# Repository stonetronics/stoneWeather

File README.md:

# stoneweather
Small IOT Weather station using Wifi Module WeMos D1 Mini, Pressure/Temperature Sensor HP03S, Relative Air Humidity/Temperature Sensor HTU21 LDO AMS1117

Newer version using WeMos D1 Mini, kicking out the ATmega328 to reduce complexity

Hardware Layout drawn in Eagle 8.0
coming soon!

Code for WeMos D1 Mini written in Arduino IDE (esp8266_d1mini_weather_station_v2)
-Measures temperature and air pressure using HP03s (custom .cpp and .h mixed up of "github.com/philippG777/HP03S" and "codebender.cc/sketch:42077#HP03S.ino"
-Measures temperature and relative air humidity using HTU21 (sparkfun Library)
-Displays all Data on a very simple Website to be used by a data collector (see github.com/ringo96/weatherstation)

Old Version using ATmega328 and ESP8266:

Hardware Layout drawn in Eagle 8.0
-Header for ESP8266 and GY21-HTU21 breakout boards mounted SMD
-all components SMD except for LED and XTAL

Code for ESP8266 written in Arduino IDE (esp8266displayUart)
-Reads temperature and air pressure on uart and displays it on a very simple website to be used by a data collector (see github.com/ringo96/weatherstation)

Code for ATMega328 written in Arduino IDE (HP03sUART)
-Measures temperature and air pressure with an HP03S sensor and displays it on uart

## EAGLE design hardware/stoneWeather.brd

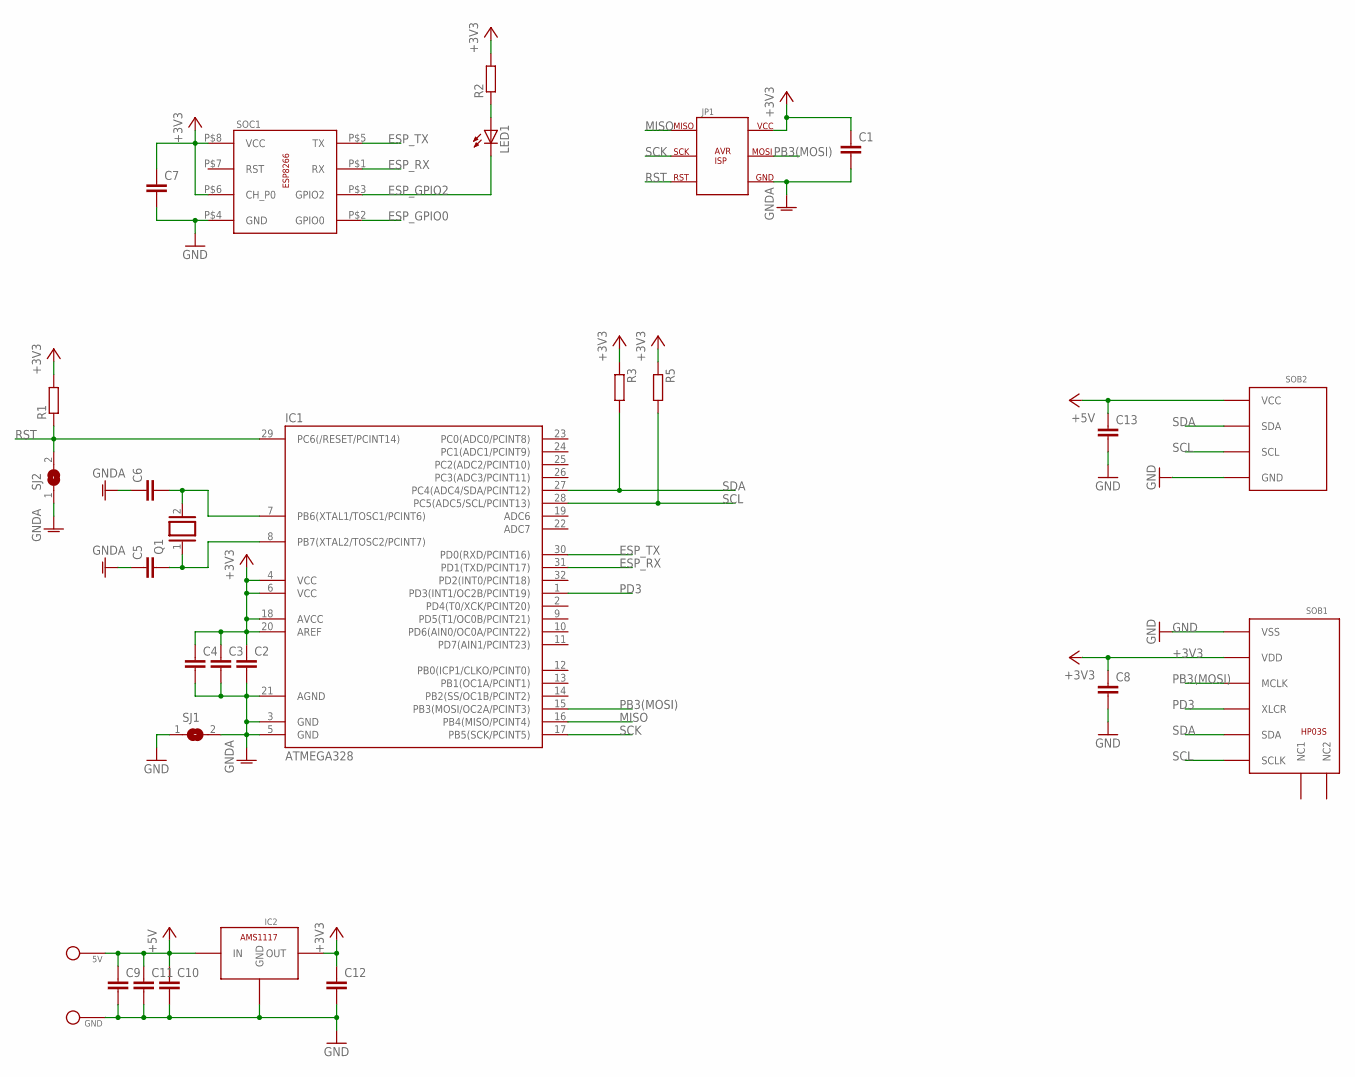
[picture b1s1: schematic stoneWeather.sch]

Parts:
5V: PAD_254X508
C1, C2, C3, C4, C5, C6, C7, C8, C9, C10, C11, C12, C13: C-EUC0805; C0805
GND: PAD_254X508
IC1: ATMEGA328; TQFP32-08
IC2: AMS1117
JP1: AVR_ISPSINGLESIDED_SMD; PINHEADER_254_2X3_SMD
LED1: LED3MM
Q1: XTAL/S; QS
R1, R2, R3, R5: R-EU_M0805; M0805
SJ1, SJ2: SJ
SOB1: HP03S
SOB2: GY21_HTU21; GY21-HTU21
SOC1: ESP8266PINHEADER_SMD; ESP8266

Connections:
+3V3: C1.1, C2.1, C3.1, C4.1, C7.1, C8.1, C12.1, IC1.4 (VCC), IC1.6 (VCC), IC1.18 (AVCC), IC1.20 (AREF), IC2.OUT, JP1.P$8 (VCC), R1.2, R2.2, R3.1, R5.1, SOB1.VDD, SOC1.P$6 (CH_P0), SOC1.P$8 (VCC)
+5V: 5V.P$1, C9.1, C10.1, C11.1, C13.1, IC2.IN, SOB2.P$4 (VCC)
ESP_GPIO0: SOC1.P$2 (GPIO0)
ESP_GPIO2: LED1.K (C), SOC1.P$3 (GPIO2)
ESP_RX: IC1.31 (PD1(TXD/PCINT17)), SOC1.P$1 (RX)
ESP_TX: IC1.30 (PD0(RXD/PCINT16)), SOC1.P$5 (TX)
GND: C7.2, C8.2, C9.2, C10.2, C11.2, C12.2, C13.2, GND.P$1, IC2.GND, SJ1.1, SOB1.VSS, SOB2.P$3 (GND), SOC1.P$4 (GND)
GNDA: C1.2, C2.2, C3.2, C4.2, C5.1, C6.1, IC1.3 (GND), IC1.5 (GND), IC1.21 (AGND), JP1.P$6 (GND), SJ1.2, SJ2.1
MISO: IC1.16 (PB4(MISO/PCINT4)), JP1.P$1 (MISO)
unnamed: LED1.A, R2.1
unnamed: C5.2, IC1.8 (PB7(XTAL2/TOSC2/PCINT7)), Q1.1
unnamed: C6.2, IC1.7 (PB6(XTAL1/TOSC1/PCINT6)), Q1.2
PB3(MOSI): IC1.15 (PB3(MOSI/OC2A/PCINT3)), JP1.P$7 (MOSI), SOB1.MCLK
PD3: IC1.1 (PD3(INT1/OC2B/PCINT19)), SOB1.XCLR (XLCR)
RST: IC1.29 (PC6(/RESET/PCINT14)), JP1.P$3 (RST), R1.1, SJ2.2
SCK: IC1.17 (PB5(SCK/PCINT5)), JP1.P$2 (SCK)
SCL: IC1.28 (PC5(ADC5/SCL/PCINT13)), R5.2, SOB1.SCLK, SOB2.P$2 (SCL)
SDA: IC1.27 (PC4(ADC4/SDA/PCINT12)), R3.2, SOB1.SDA, SOB2.P$1 (SDA)

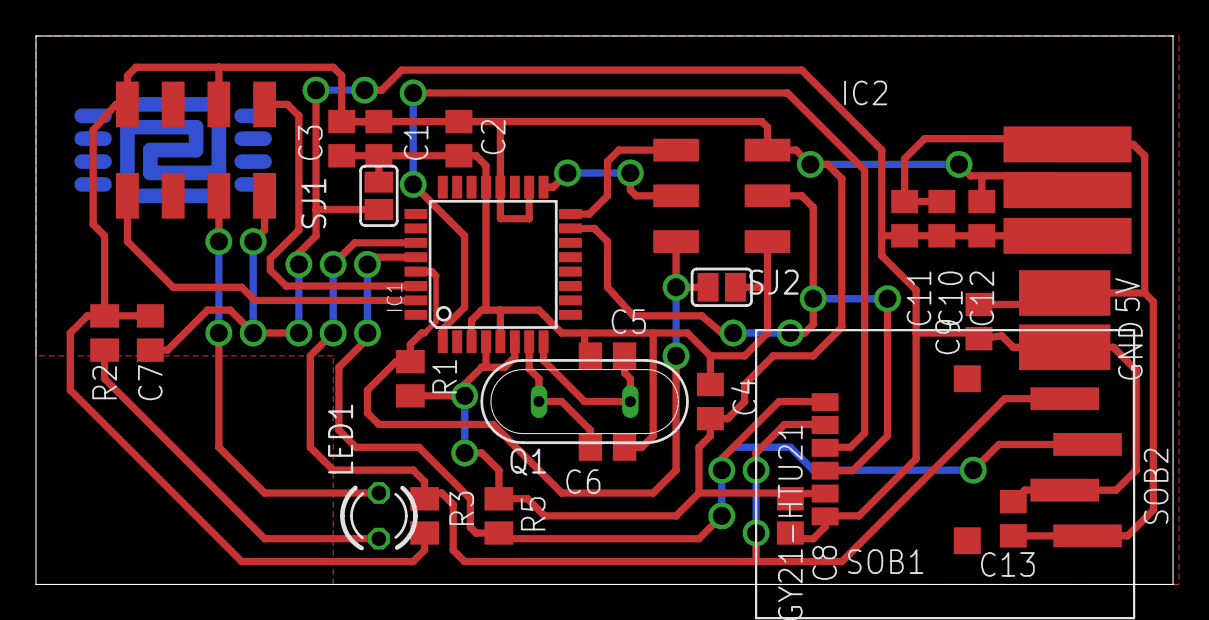
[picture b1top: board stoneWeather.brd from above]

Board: 2 copper layers, 63.2 x 30.5 mm, 29 parts (0 on the bottom side), 17 nets.

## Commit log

2017-09-17 updated first working version of the esp8266 and the atmega328 firmware
2017-09-17 Added GY21-HTU21 breakout board header to the board Updated README.md
2017-09-28 Updated to use with WeMos D1 mini, kicking out the ATMega328, implementation of HTU21d using Sparkfun library
